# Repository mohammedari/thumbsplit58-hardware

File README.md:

# Thumbsplit58 Hardware
File archive for Thumbsplit58 keyboard PCB and case. You may also want to refer [Nordic MCU firmware](https://github.com/mohammedari/thumbsplit58-firmware) and [qmk_firmware](https://github.com/mohammedari/qmk_firmware/blob/oneoff/thumbsplit58/keyboards/thumbsplit58/) repository.

This repository only contains PCB gerber files for keyboard itself. 
You can use [Comet46's receiver gerber files](https://github.com/satt100/comet46-hardware.git) to make receiver for this keyboard.

## Top plates

Top plate DXF files are available under [dxf](dxf) directory.
This design is intended to be milled using 2mm endmill, 
but it should be manufacturable by laser cutters.

|                        | Left                                 | Right                                  |
| ---------------------- | ------------------------------------ | -------------------------------------- |
| rev1 (1u/1.5u support) |       |       |
| rev2 (1.5u only)       |  |  |

## Case

Case STL files are available under [stl](stl) directory.
This design is intended to be 3D printed using SLS (Selective Laser Sintering) or SLA (Stereolithography) printer.
It may be printable by FDM (Fused Deposition Modeling) printers, but probably requires additional work.

|               | Left                                   | Right                                    |
| ------------- | -------------------------------------- | ---------------------------------------- |
| rev1 (CR2032) |       |       |
| rev2 (AA)     |  |  |

## Gerber files

Gerber files are available under [gerber](gerber) directory. 
These archives follow Fusion PCB's design guideline and output instruction.

## Schematics

- [Right half](schematic/thumb-split-right-v1.0.pdf)
- [Left half](schematic/thumb-split-left-v1.0.pdf)

## Parts list

TODO

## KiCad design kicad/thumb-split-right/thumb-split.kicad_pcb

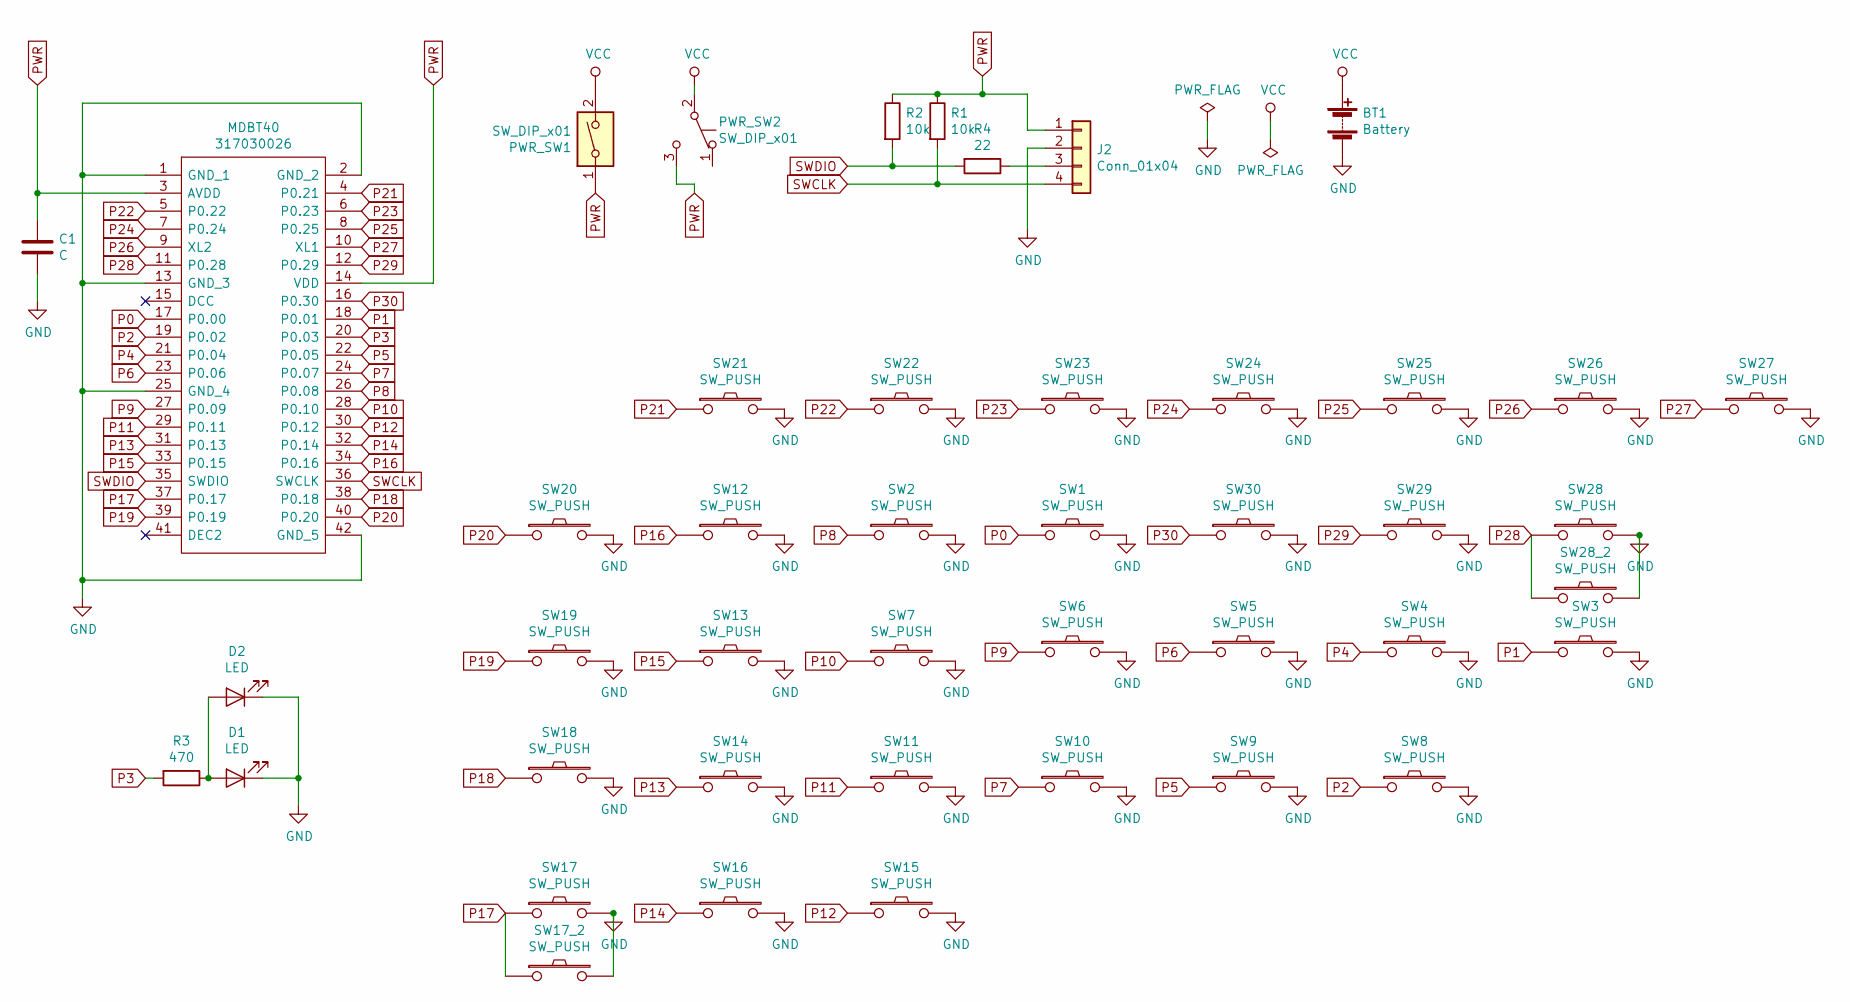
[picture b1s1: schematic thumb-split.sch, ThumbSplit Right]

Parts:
BT1: Battery; bhsd-2032
C1: C; C_0805_2012Metric_Pad1.15x1.40mm_HandSolder
D1, D2: LED; LED_0603_1608Metric_Pad1.05x0.95mm_HandSolder
J2: Conn_01x04; conn_throuth_01x04
MDBT40: 317030026; Manufacturer_Part_Number 317030026; Mouser Part Number 713-317030026
PWR_SW1, PWR_SW2: SW_DIP_x01; EG1257
R1, R2: 10k; R_0603_1608Metric_Pad1.05x0.95mm_HandSolder
R3: 470; R_0603_1608Metric_Pad1.05x0.95mm_HandSolder
R4: 22; R_0603_1608Metric_Pad1.05x0.95mm_HandSolder
SW1, SW2, SW3, SW4, SW5, SW6, SW7, SW8, SW9, SW10, SW11, SW12, SW13, SW14, SW15, SW16, SW17_2, SW18, SW19, SW20, SW21, SW22, SW23, SW24, SW25, SW26, SW27, SW28, SW28_2, SW29, SW30: SW_PUSH; Choc_Hotswap_1side
SW17: SW_PUSH; Choc_Hotswap_1side_1.5u

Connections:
GND: BT1.2 (-), C1.2, D1.1 (K), D2.1 (K), J2.2, MDBT40.1 (GND_1), MDBT40.2 (GND_2), MDBT40.13 (GND_3), MDBT40.25 (GND_4), MDBT40.42 (GND_5), SW1.2, SW2.2, SW3.2, SW4.2, SW5.2, SW6.2, SW7.2, SW8.2, SW9.2, SW10.2, SW11.2, SW12.2, SW13.2, SW14.2, SW15.2, SW16.2, SW17.2, SW17_2.2, SW18.2, SW19.2, SW20.2, SW21.2, SW22.2, SW23.2, SW24.2, SW25.2, SW26.2, SW27.2, SW28.2, SW28_2.2, SW29.2, SW30.2
unnamed: D1.2 (A), D2.2 (A), R3.1
unnamed: J2.3, R4.1
P0: MDBT40.17 (P0.00), SW1.1
P1: MDBT40.18 (P0.01), SW3.1
P2: MDBT40.19 (P0.02), SW8.1
P3: MDBT40.20 (P0.03), R3.2
P4: MDBT40.21 (P0.04), SW4.1
P5: MDBT40.22 (P0.05), SW9.1
P6: MDBT40.23 (P0.06), SW5.1
P7: MDBT40.24 (P0.07), SW10.1
P8: MDBT40.26 (P0.08), SW2.1
P9: MDBT40.27 (P0.09), SW6.1
P10: MDBT40.28 (P0.10), SW7.1
P11: MDBT40.29 (P0.11), SW11.1
P12: MDBT40.30 (P0.12), SW15.1
P13: MDBT40.31 (P0.13), SW14.1
P14: MDBT40.32 (P0.14), SW16.1
P15: MDBT40.33 (P0.15), SW13.1
P16: MDBT40.34 (P0.16), SW12.1
P17: MDBT40.37 (P0.17), SW17.1, SW17_2.1
P18: MDBT40.38 (P0.18), SW18.1
P19: MDBT40.39 (P0.19), SW19.1
P20: MDBT40.40 (P0.20), SW20.1
P21: MDBT40.4 (P0.21), SW21.1
P22: MDBT40.5 (P0.22), SW22.1
P23: MDBT40.6 (P0.23), SW23.1
P24: MDBT40.7 (P0.24), SW24.1
P25: MDBT40.8 (P0.25), SW25.1
P26: MDBT40.9 (XL2), SW26.1
P27: MDBT40.10 (XL1), SW27.1
P28: MDBT40.11 (P0.28), SW28.1, SW28_2.1
P29: MDBT40.12 (P0.29), SW29.1
P30: MDBT40.16 (P0.30), SW30.1
PWR: C1.1, J2.1, MDBT40.3 (AVDD), MDBT40.14 (VDD), PWR_SW1.1, PWR_SW2.3 (C), R1.1, R2.1
SWCLK: J2.4, MDBT40.36 (SWCLK), R1.2
SWDIO: MDBT40.35 (SWDIO), R2.2, R4.2
VCC: BT1.1 (+), PWR_SW1.2, PWR_SW2.2 (B)

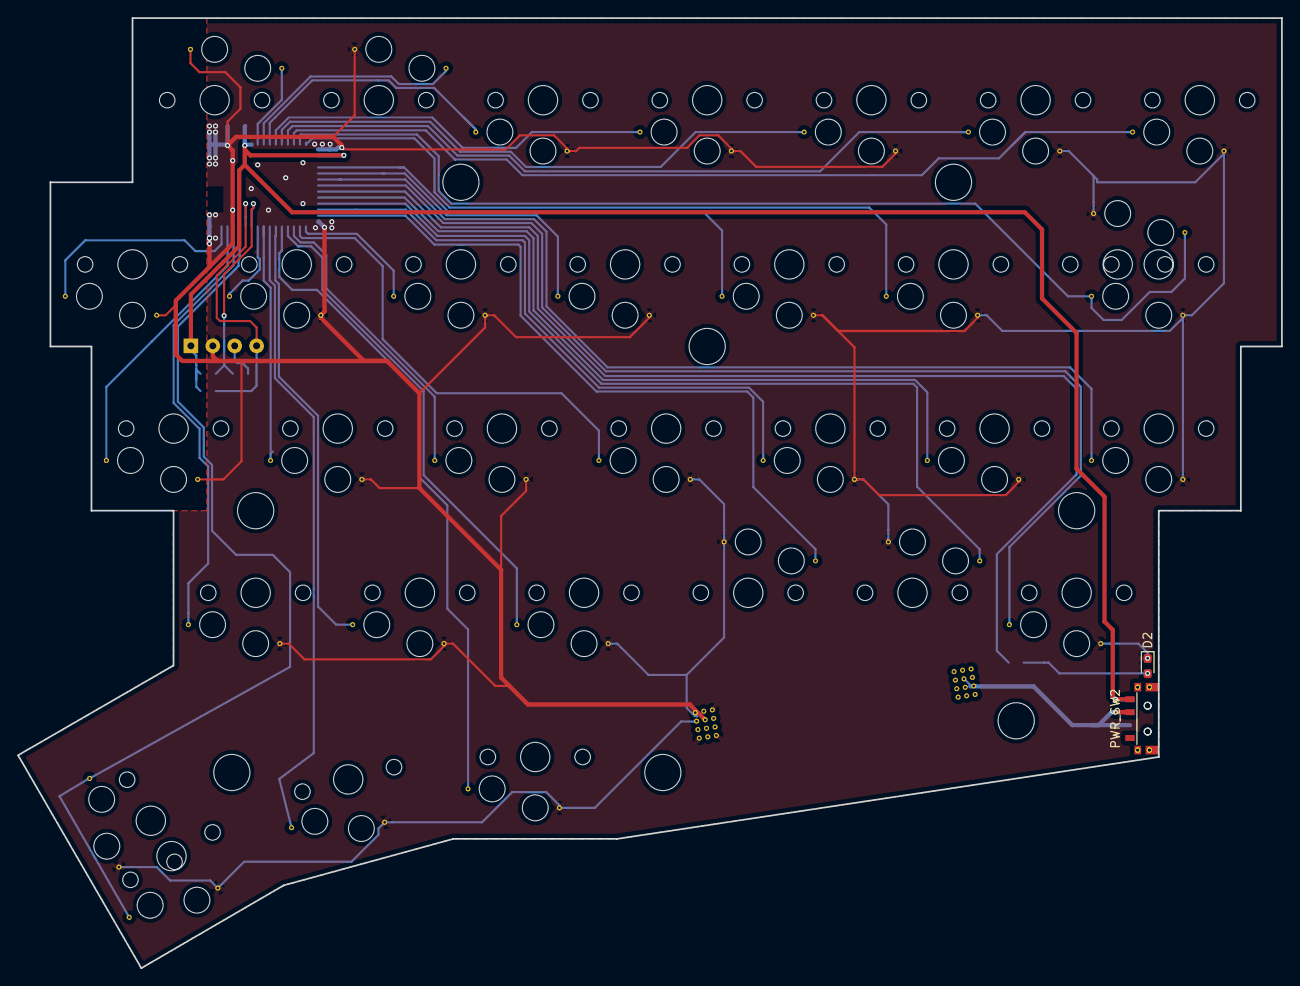
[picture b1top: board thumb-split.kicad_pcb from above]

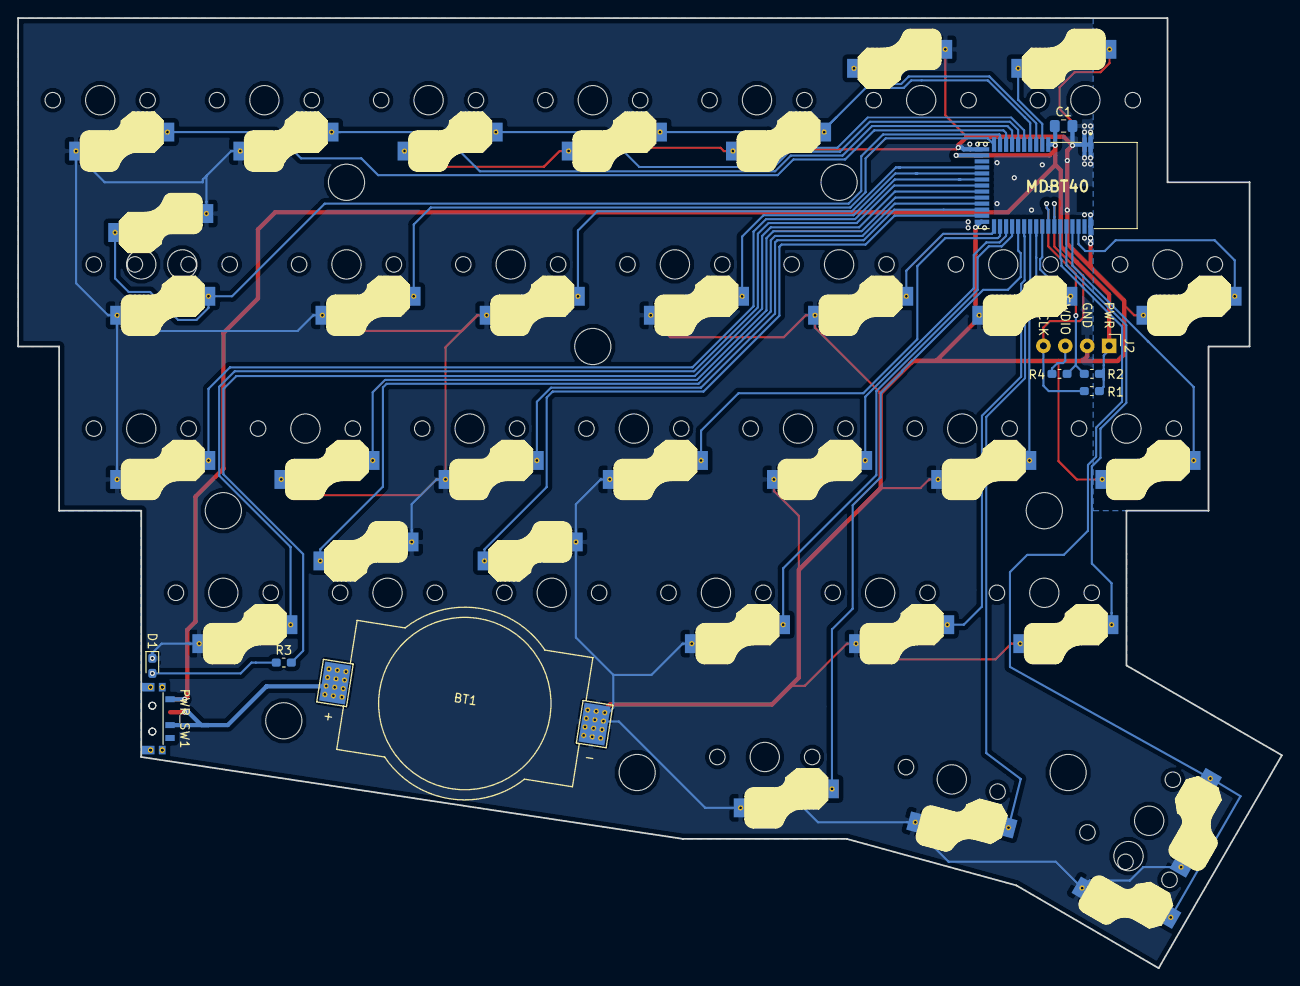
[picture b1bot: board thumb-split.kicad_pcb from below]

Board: 2 copper layers, 146.6 x 110.2 mm, 44 parts (10 on the bottom side), 38 nets.

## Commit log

2020-12-29 added files
2020-12-29 fix link issue in readme
2021-02-10 added kicad project files
